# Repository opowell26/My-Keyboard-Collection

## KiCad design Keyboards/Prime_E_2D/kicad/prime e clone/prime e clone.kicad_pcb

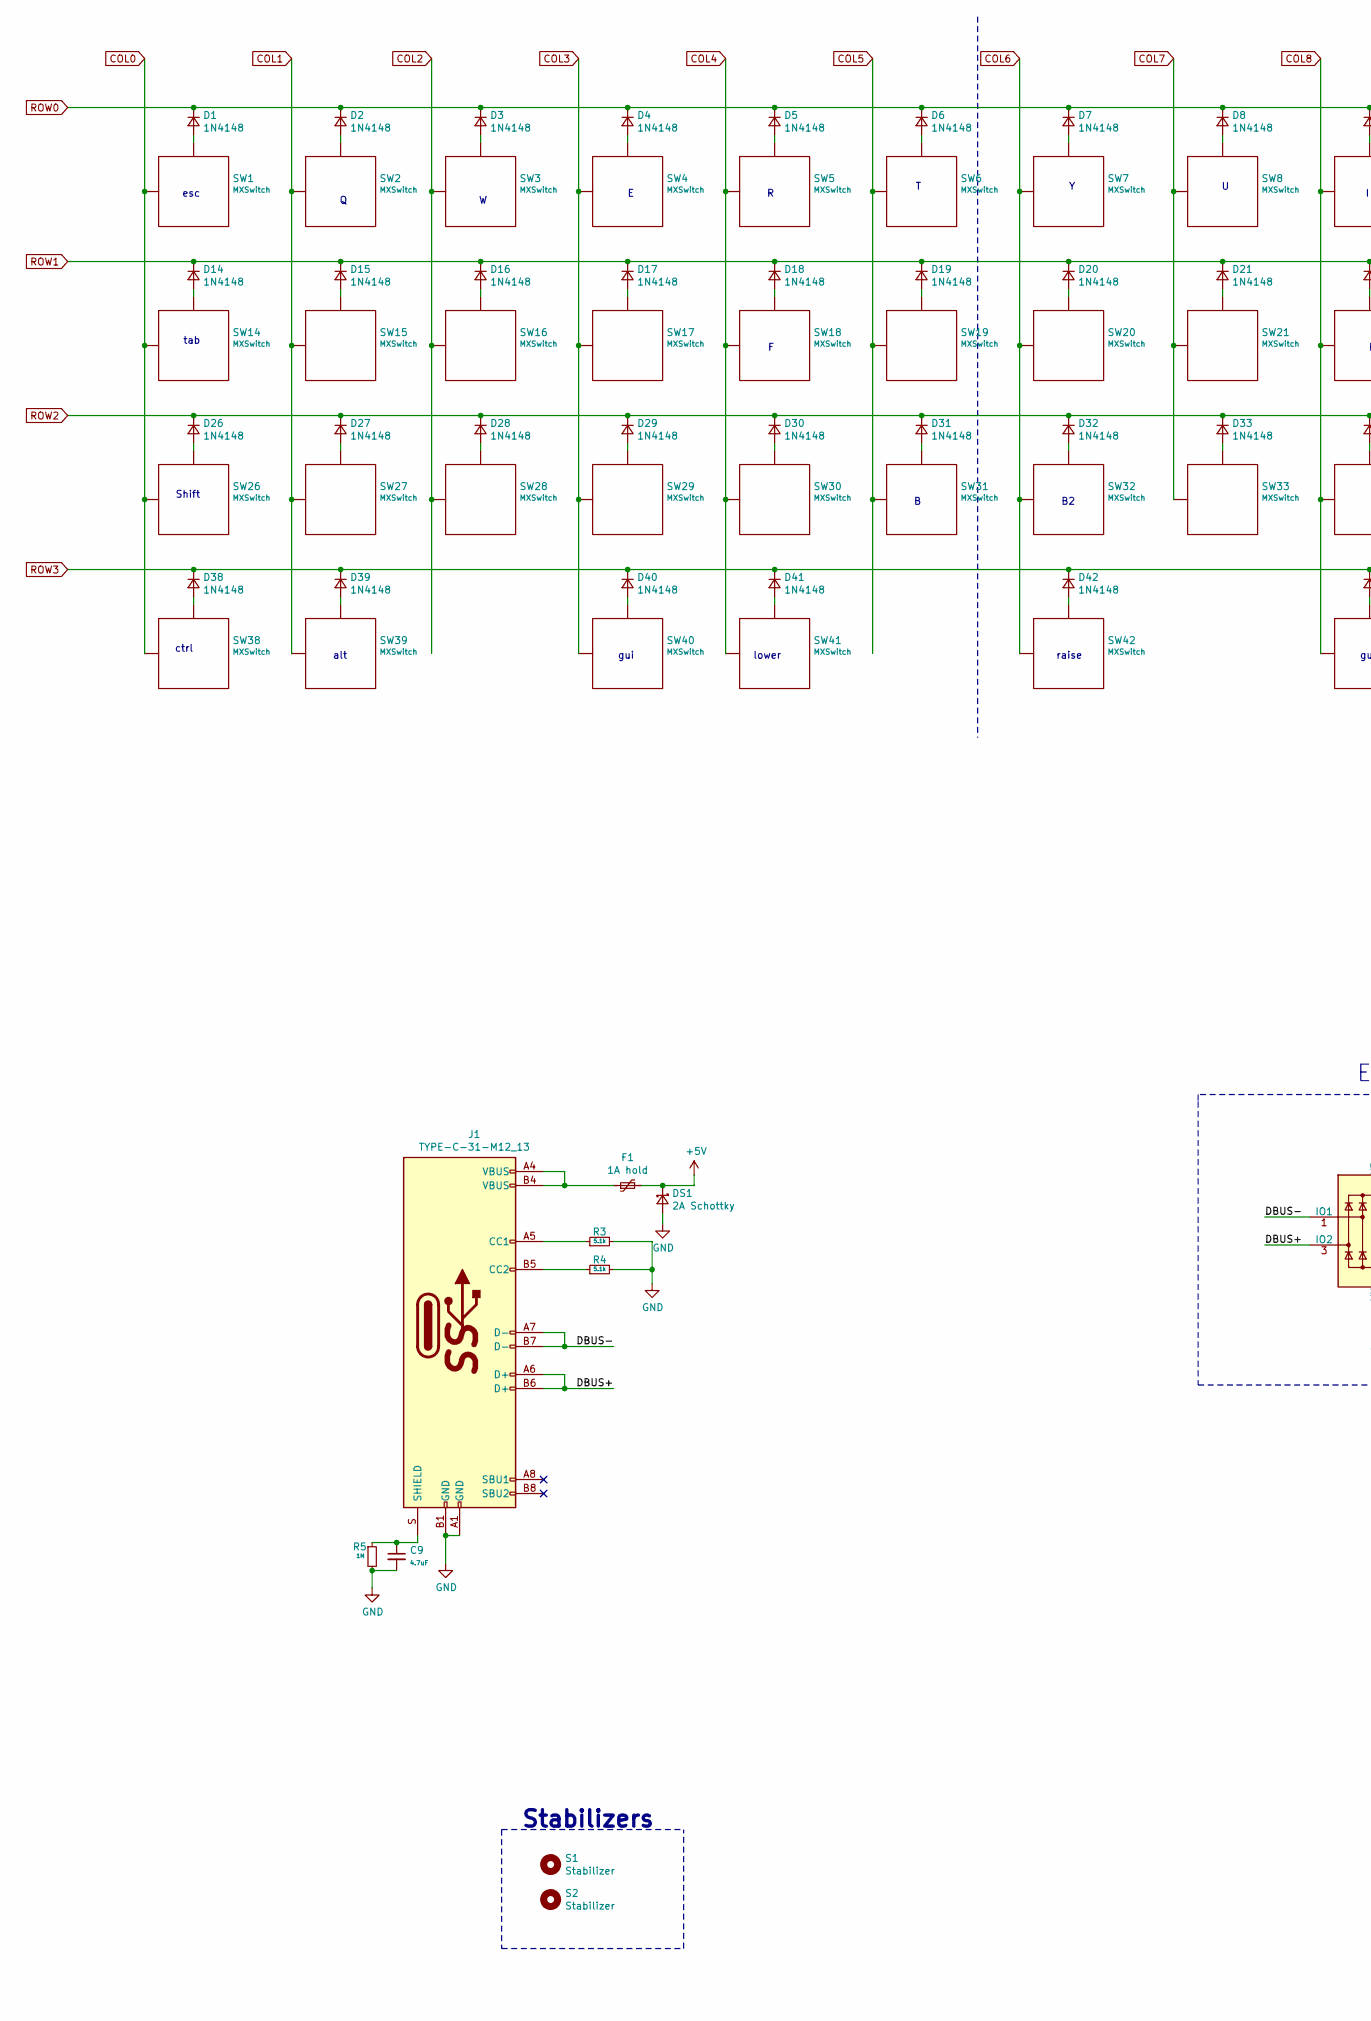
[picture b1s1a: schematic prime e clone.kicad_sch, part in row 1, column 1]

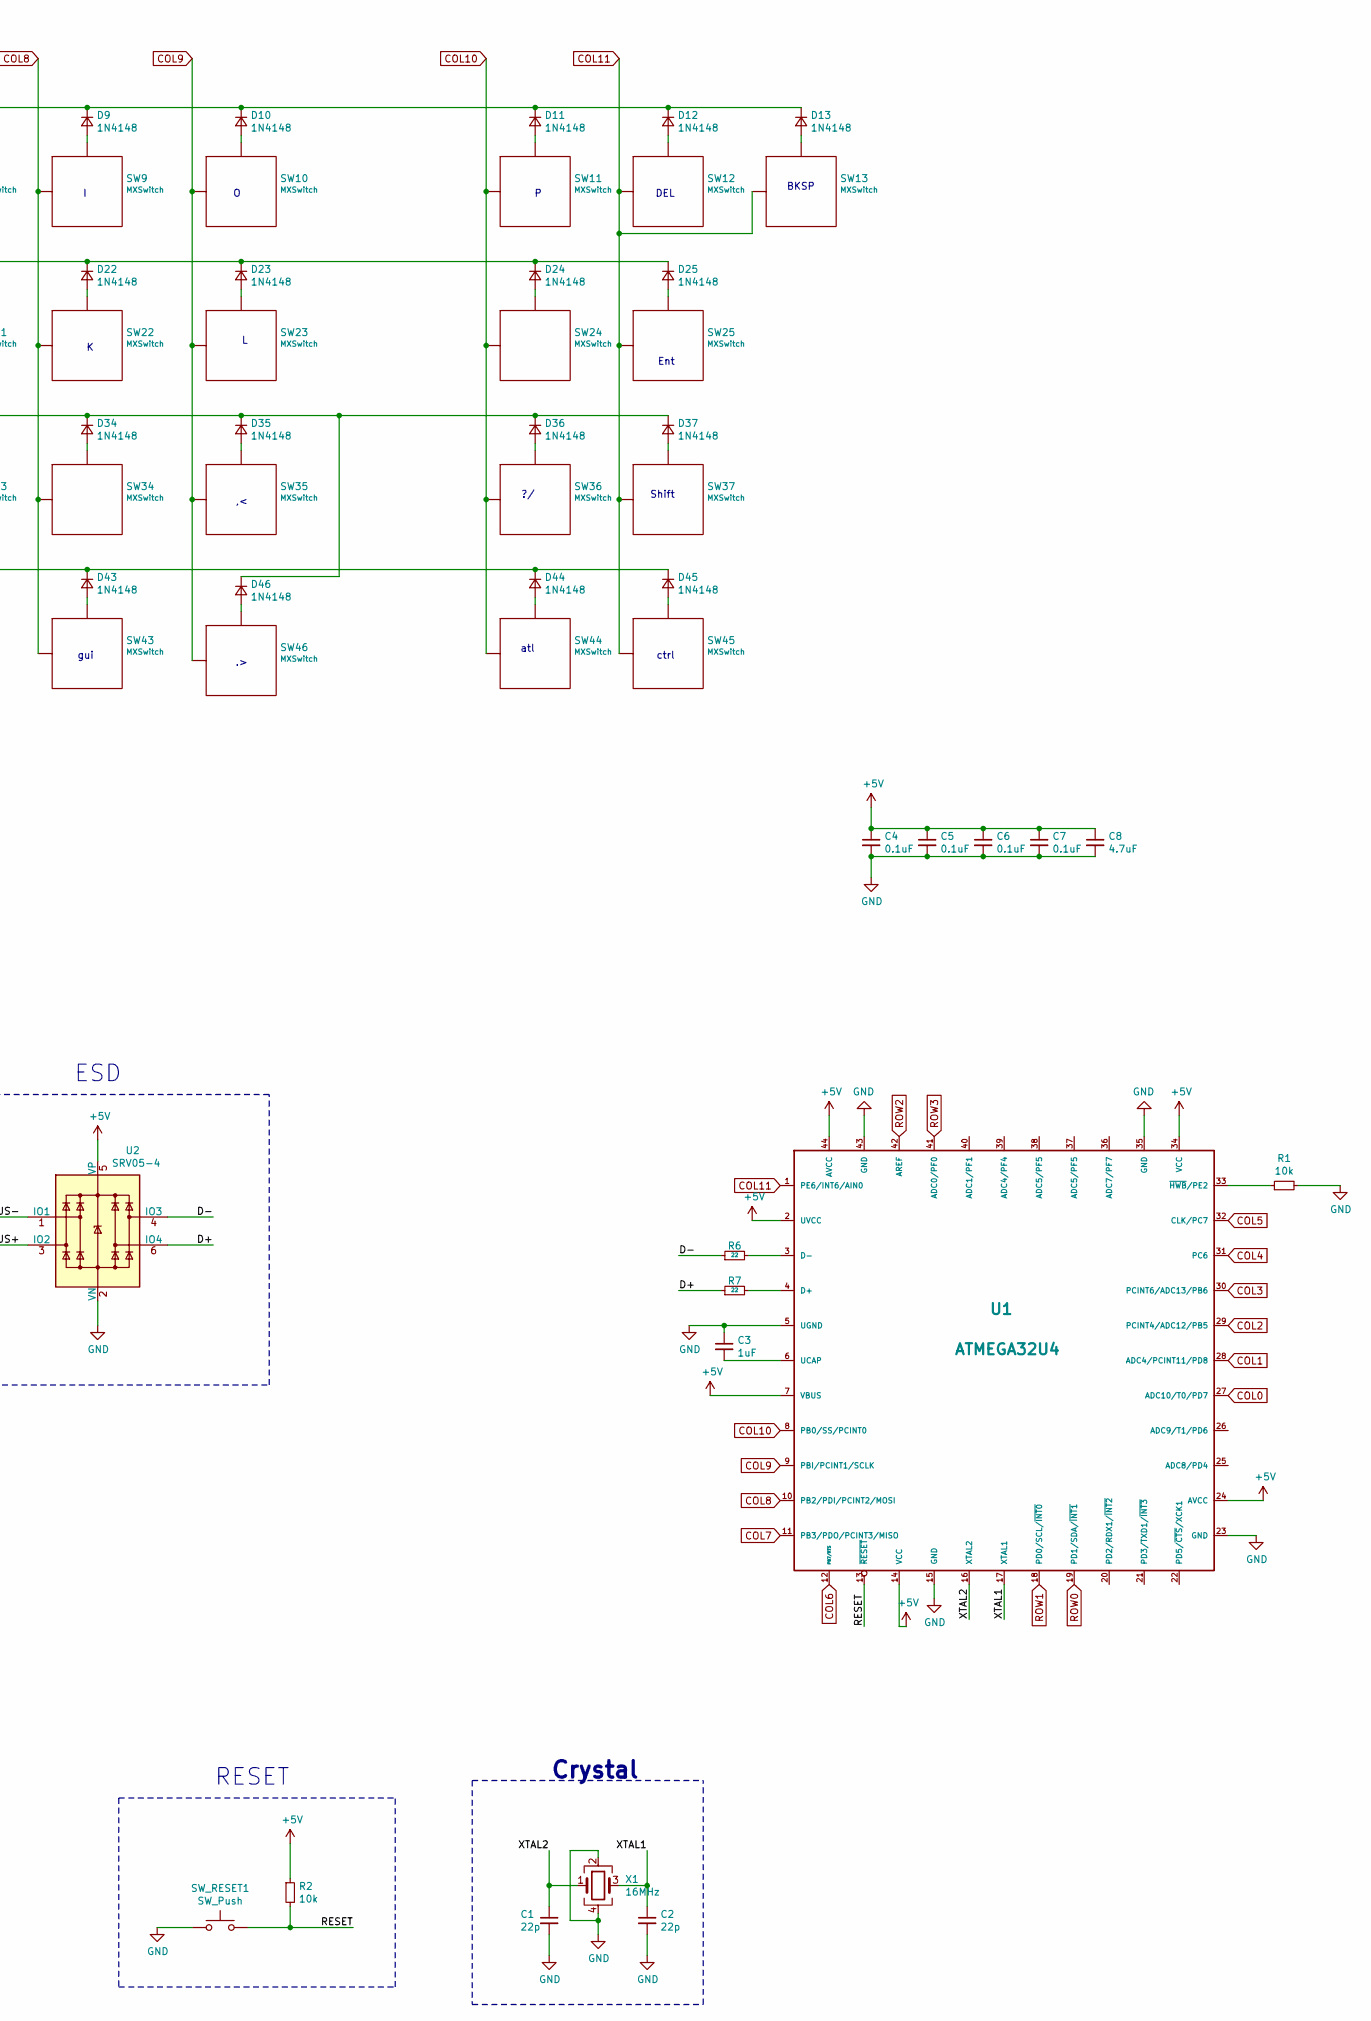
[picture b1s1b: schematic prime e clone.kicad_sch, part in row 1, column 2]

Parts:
C1, C2: 22p; C_0805_2012Metric; LCSC C1804
C3: 1uF; C_0805_2012Metric; LCSC C28323
C4, C5, C6, C7: 0.1uF; C_0805_2012Metric; LCSC C49678
C8, C9: 4.7uF; C_0805_2012Metric; LCSC C1779
D1, D2, D3, D4, D5, D6, D7, D8, D9, D10, D11, D12, D13, D14, D15, D16, D17, D18, D19, D20, D21, D22, D23, D24, D25, D26, D27, D28, D29, D30, D31, D32, D33, D34, D35, D36, D37, D38, D39, D40, D41, D42, D43, D44, D45, D46: 1N4148; D_SOD-323_HandSoldering; LCSC C2128
DS1: 2A Schottky; D_SOD-123; LCSC C14996
F1: 1A hold; Fuse_1206_3216Metric; LCSC C70082
J1: TYPE-C-31-M12_13; TYPE-C-31-M-12; LCSC C165948
R1, R2: 10k; R_0805_2012Metric; LCSC C17414
R3, R4: 5.1k; R_0402_1005Metric; LCSC C25905
R5: 1M; R_0805_2012Metric; LCSC C17514
R6, R7: 22; R_0805_2012Metric; LCSC C17561
S1, S2: Stabilizer; Stabilizer_MX_2u
SW1, SW2, SW3, SW4, SW5, SW6, SW7, SW8, SW9, SW10, SW11, SW12, SW13, SW14, SW15, SW16, SW17, SW18, SW19, SW20, SW21, SW22, SW23, SW24, SW25, SW26, SW27, SW28, SW29, SW30, SW31, SW32, SW33, SW34, SW35, SW36, SW37, SW38, SW39, SW40, SW41, SW42, SW43, SW44, SW45, SW46: MXSwitch; Kailh_socket_MX
SW_RESET1: SW_Push; SW_SPST_TL3342; LCSC C318884
U1: ATMEGA32U4; TQPF-44_10x10mm_P0.8mm; LCSC C112161
U2: SRV05-4; SOT-23-6; LCSC C85364
X1: 16MHz; Crystal_SMD_3225-4Pin_3.2x2.5mm; LCSC C13738

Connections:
+5V: C4.1, C5.1, C6.1, C7.1, C8.1, DS1.1 (K), F1.2, R2.1, U1.2 (UVCC), U1.7 (VBUS), U1.14 (VCC), U1.24 (AVCC), U1.34 (VCC), U1.44 (AVCC), U2.5 (VP)
/D+: R7.1, U2.6 (IO4)
/D-: R6.1, U2.4 (IO3)
/DBUS+: J1.A6 (D+), J1.B6 (D+), U2.3 (IO2)
/DBUS-: J1.A7 (D-), J1.B7 (D-), U2.1 (IO1)
/RESET: R2.2, SW_RESET1.2, U1.13 (~RESET~)
/XTAL1: C2.1, U1.17 (XTAL1), X1.3
/XTAL2: C1.1, U1.16 (XTAL2), X1.1
COL0: SW1.1 (Col), SW14.1 (Col), SW26.1 (Col), SW38.1 (Col), U1.27 (ADC10/T0/PD7)
COL1: SW2.1 (Col), SW15.1 (Col), SW27.1 (Col), SW39.1 (Col), U1.28 (ADC4/PCINT11/PD8)
COL2: SW3.1 (Col), SW16.1 (Col), SW28.1 (Col), U1.29 (PCINT4/ADC12/PB5)
COL3: SW4.1 (Col), SW17.1 (Col), SW29.1 (Col), SW40.1 (Col), U1.30 (PCINT6/ADC13/PB6)
COL4: SW5.1 (Col), SW18.1 (Col), SW30.1 (Col), SW41.1 (Col), U1.31 (PC6)
COL5: SW6.1 (Col), SW19.1 (Col), SW31.1 (Col), U1.32 (CLK/PC7)
COL6: SW7.1 (Col), SW20.1 (Col), SW32.1 (Col), SW42.1 (Col), U1.12 (PB7/RTS)
COL7: SW8.1 (Col), SW21.1 (Col), SW33.1 (Col), U1.11 (PB3/PDO/PCINT3/MISO)
COL8: SW9.1 (Col), SW22.1 (Col), SW34.1 (Col), SW43.1 (Col), U1.10 (PB2/PDI/PCINT2/MOSI)
COL9: SW10.1 (Col), SW23.1 (Col), SW35.1 (Col), SW46.1 (Col), U1.9 (PBI/PCINT1/SCLK)
COL10: SW11.1 (Col), SW24.1 (Col), SW36.1 (Col), SW44.1 (Col), U1.8 (PB0/SS/PCINT0)
COL11: SW12.1 (Col), SW13.1 (Col), SW25.1 (Col), SW37.1 (Col), SW45.1 (Col), U1.1 (PE6/INT6/AIN0)
GND: C1.2, C2.2, C3.1, C4.2, C5.2, C6.2, C7.2, C8.2, C9.2, DS1.2 (A), J1.A1 (GND), J1.B1 (GND), R1.2, R3.2, R4.2, R5.2, SW_RESET1.1, U1.5 (UGND), U1.15 (GND), U1.23 (GND), U1.35 (GND), U1.43 (GND), U2.2 (VN), X1.2, X1.4
unnamed: C3.2, U1.6 (UCAP)
unnamed: C9.1, J1.S (SHIELD), R5.1
unnamed: D1.2 (A), SW1.2 (Row)
unnamed: D2.2 (A), SW2.2 (Row)
unnamed: D3.2 (A), SW3.2 (Row)
unnamed: D4.2 (A), SW4.2 (Row)
unnamed: D5.2 (A), SW5.2 (Row)
unnamed: D6.2 (A), SW6.2 (Row)
unnamed: D7.2 (A), SW7.2 (Row)
unnamed: D8.2 (A), SW8.2 (Row)
unnamed: D9.2 (A), SW9.2 (Row)
unnamed: D10.2 (A), SW10.2 (Row)
unnamed: D11.2 (A), SW11.2 (Row)
unnamed: D12.2 (A), SW12.2 (Row)
unnamed: D13.2 (A), SW13.2 (Row)
unnamed: D14.2 (A), SW14.2 (Row)
unnamed: D15.2 (A), SW15.2 (Row)
unnamed: D16.2 (A), SW16.2 (Row)
unnamed: D17.2 (A), SW17.2 (Row)
unnamed: D18.2 (A), SW18.2 (Row)
unnamed: D19.2 (A), SW19.2 (Row)
unnamed: D20.2 (A), SW20.2 (Row)
unnamed: D21.2 (A), SW21.2 (Row)
unnamed: D22.2 (A), SW22.2 (Row)
unnamed: D23.2 (A), SW23.2 (Row)
unnamed: D24.2 (A), SW24.2 (Row)
unnamed: D25.2 (A), SW25.2 (Row)
unnamed: D26.2 (A), SW26.2 (Row)
unnamed: D27.2 (A), SW27.2 (Row)
unnamed: D28.2 (A), SW28.2 (Row)
unnamed: D29.2 (A), SW29.2 (Row)
unnamed: D30.2 (A), SW30.2 (Row)
unnamed: D31.2 (A), SW31.2 (Row)
unnamed: D32.2 (A), SW32.2 (Row)
unnamed: D33.2 (A), SW33.2 (Row)
unnamed: D34.2 (A), SW34.2 (Row)
unnamed: D35.2 (A), SW35.2 (Row)
unnamed: D36.2 (A), SW36.2 (Row)
unnamed: D37.2 (A), SW37.2 (Row)
unnamed: D38.2 (A), SW38.2 (Row)
unnamed: D39.2 (A), SW39.2 (Row)
unnamed: D40.2 (A), SW40.2 (Row)
unnamed: D41.2 (A), SW41.2 (Row)
unnamed: D42.2 (A), SW42.2 (Row)
unnamed: D43.2 (A), SW43.2 (Row)
unnamed: D44.2 (A), SW44.2 (Row)
unnamed: D45.2 (A), SW45.2 (Row)
unnamed: D46.2 (A), SW46.2 (Row)
unnamed: F1.1, J1.A4 (VBUS), J1.B4 (VBUS)
unnamed: J1.A5 (CC1), R3.1
unnamed: J1.B5 (CC2), R4.1
unnamed: R1.1, U1.33 (~HWB~/PE2)
unnamed: R6.2, U1.3 (D-)
unnamed: R7.2, U1.4 (D+)
ROW0: D1.1 (K), D2.1 (K), D3.1 (K), D4.1 (K), D5.1 (K), D6.1 (K), D7.1 (K), D8.1 (K), D9.1 (K), D10.1 (K), D11.1 (K), D12.1 (K), D13.1 (K), U1.19 (PD1/SDA/~INT1~)
ROW1: D14.1 (K), D15.1 (K), D16.1 (K), D17.1 (K), D18.1 (K), D19.1 (K), D20.1 (K), D21.1 (K), D22.1 (K), D23.1 (K), D24.1 (K), D25.1 (K), U1.18 (PD0/SCL/~INT0~)
ROW2: D26.1 (K), D27.1 (K), D28.1 (K), D29.1 (K), D30.1 (K), D31.1 (K), D32.1 (K), D33.1 (K), D34.1 (K), D35.1 (K), D36.1 (K), D37.1 (K), D46.1 (K), U1.42 (AREF)
ROW3: D38.1 (K), D39.1 (K), D40.1 (K), D41.1 (K), D42.1 (K), D43.1 (K), D44.1 (K), D45.1 (K), U1.41 (ADC0/PF0)

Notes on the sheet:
ctrl
esc
tab
Shift
alt
gui
Stabilizers
lower
raise
ESD
RESET
atl
Crystal
DEL
Ent
Shift
BKSP

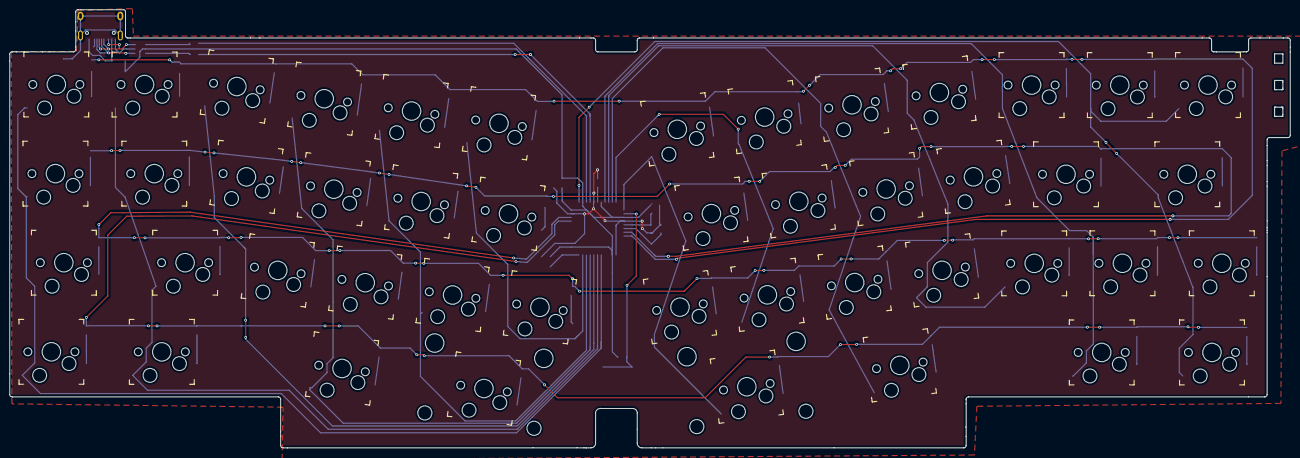
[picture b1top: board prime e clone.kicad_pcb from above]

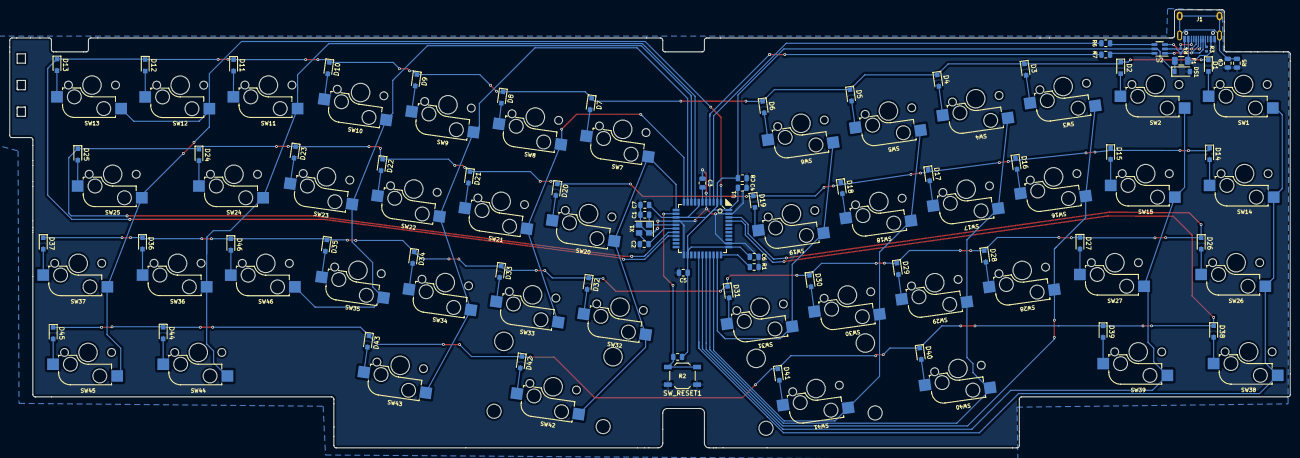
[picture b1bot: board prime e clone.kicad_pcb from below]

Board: 2 copper layers, 276.5 x 94.6 mm, 117 parts (69 on the bottom side), 79 nets.

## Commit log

2022-02-05 Collection of keyboards from my PC
